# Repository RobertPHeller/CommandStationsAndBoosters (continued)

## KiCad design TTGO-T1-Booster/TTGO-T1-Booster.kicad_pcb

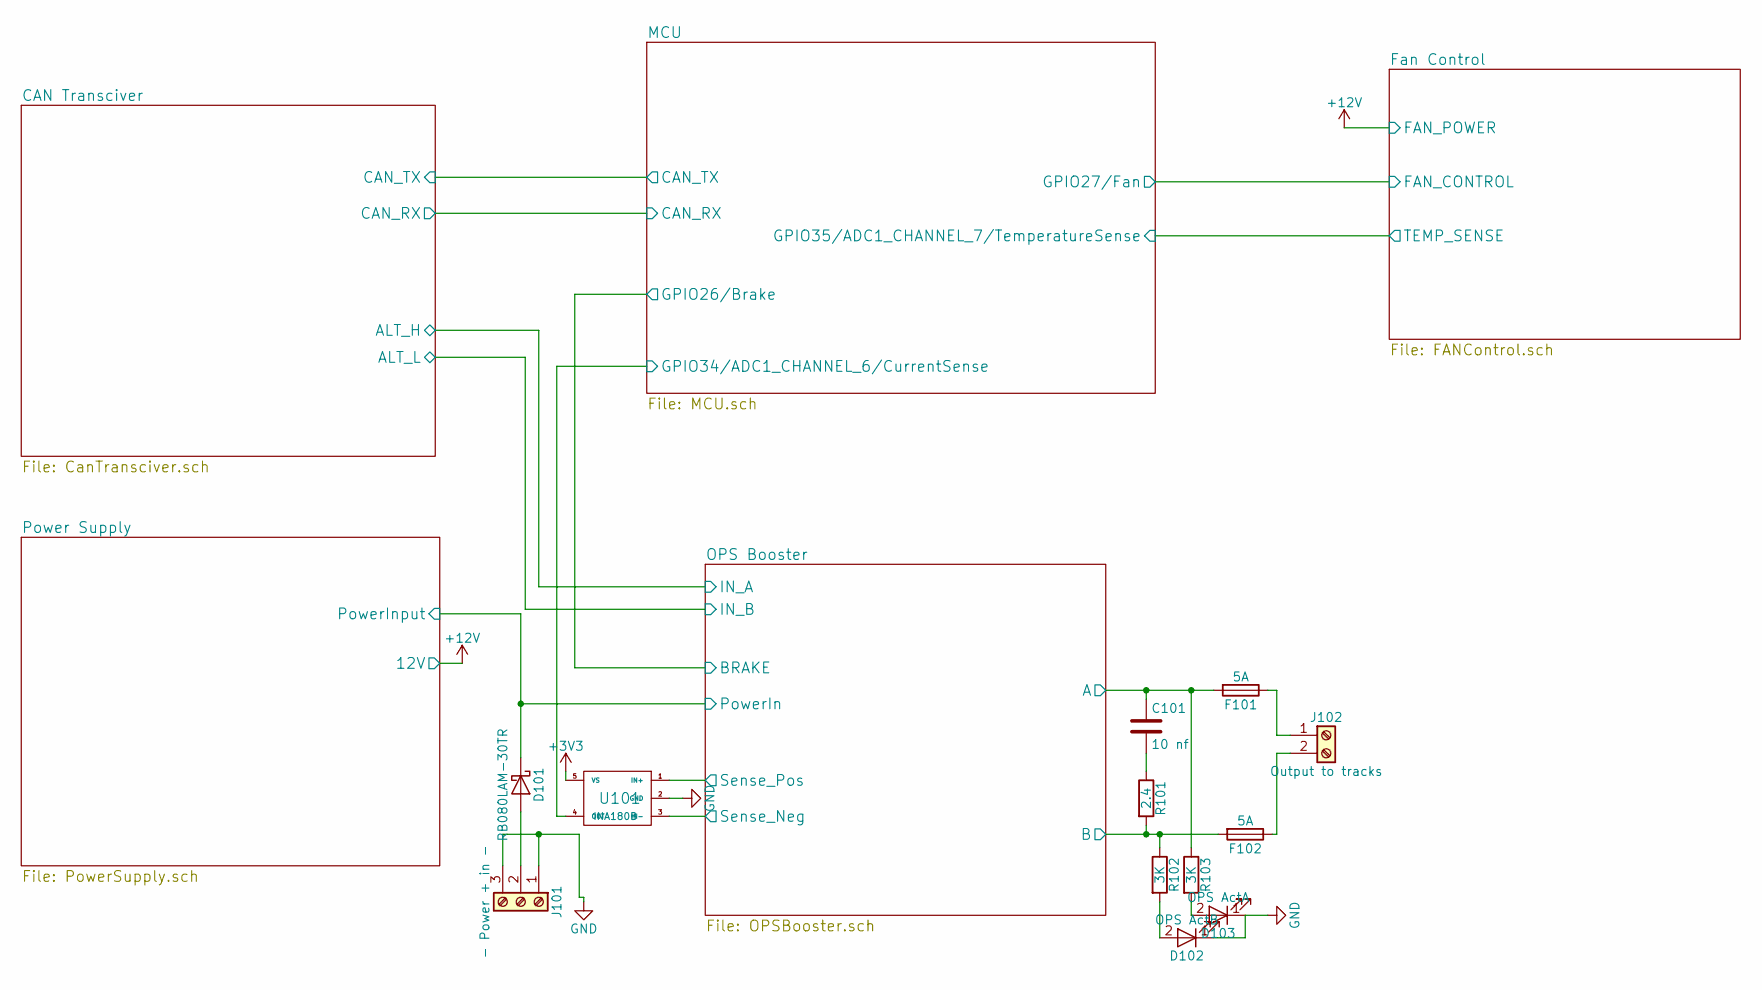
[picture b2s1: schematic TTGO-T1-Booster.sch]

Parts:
C101: 10 nf; C_1206; Mouser Part Number 791-1206B103K500CT
D101: RB080LAM-30TR; PMDTM; Mouser Part Number 755-RB080LAM-30TR
D102: OPS ActB; LED_0603; Mouser Part Number 710-150060RS75000
D103: OPS ActA; LED_0603; Mouser Part Number 710-150060GS75000
F101, F102: 5A; MFR500; Mouser Part Number 652-MFR500
J101: - Power + in -; TerminalBlock_Pheonix_PT-3.5mm_3pol; Mouser Part Number 651-544225
J102: Output to tracks; TerminalBlock_Pheonix_PT-3.5mm_2pol; Mouser Part Number 651-5442248
R101: 2.4; R_1206; Mouser Part Number 71-CRCW12062R40FKEA
R102: 3K; R_0603
R103: 3K; R_0603; Mouser Part Number 660-RN73H1JT3001F100
U101: INA180B; SOT-23-5

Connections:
/MCU/GPIO34/ADC1_CHANNEL_6/CurrentSense: U101.4 (OUT); also elsewhere on the board
/OPS Booster/A: C101.1, F101.2, R103.1; also elsewhere on the board
/OPS Booster/B: F102.2, R101.2, R102.1; also elsewhere on the board
/OPS Booster/PowerIn: D101.1 (K), U101.1 (IN+); also elsewhere on the board
/OPS Booster/Sense_Neg: U101.3 (IN-); also elsewhere on the board
GND: D102.1 (K), D103.1 (K), J101.1, J101.3, U101.2 (GND); also elsewhere on the board
unnamed: C101.2, R101.1
unnamed: D101.2 (A), J101.2
unnamed: D102.2 (A), R102.2
unnamed: D103.2 (A), R103.2
unnamed: F101.1, J102.1
unnamed: F102.1, J102.2

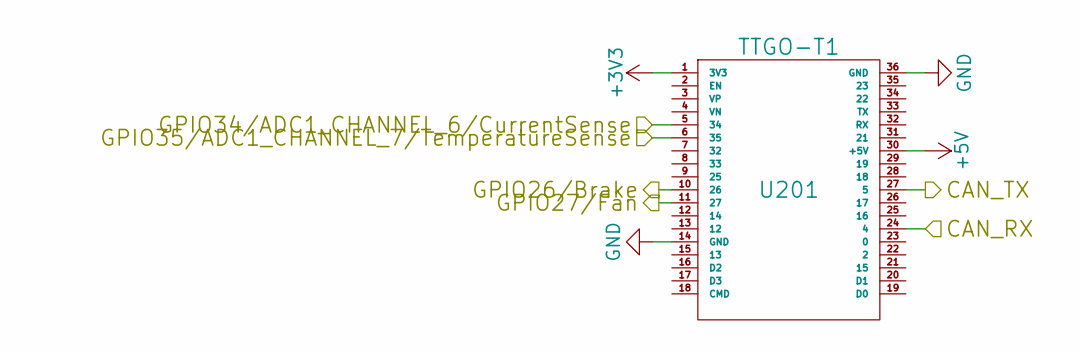
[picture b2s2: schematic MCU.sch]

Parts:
U201: TTGO-T1; TIGO-T1

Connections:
+5V: U201.30 (+5V); also elsewhere on the board
/CAN Transciver/CAN_RX: U201.24 (4); also elsewhere on the board
/CAN Transciver/CAN_TX: U201.27 (5); also elsewhere on the board
/Fan Control/FAN_CONTROL: U201.11 (27); also elsewhere on the board
/MCU/GPIO34/ADC1_CHANNEL_6/CurrentSense: U201.5 (34); also elsewhere on the board
/MCU/GPIO35/ADC1_CHANNEL_7/TemperatureSense: U201.6 (35); also elsewhere on the board
/OPS Booster/BRAKE: U201.10 (26); also elsewhere on the board
GND: U201.14 (GND), U201.36 (GND); also elsewhere on the board

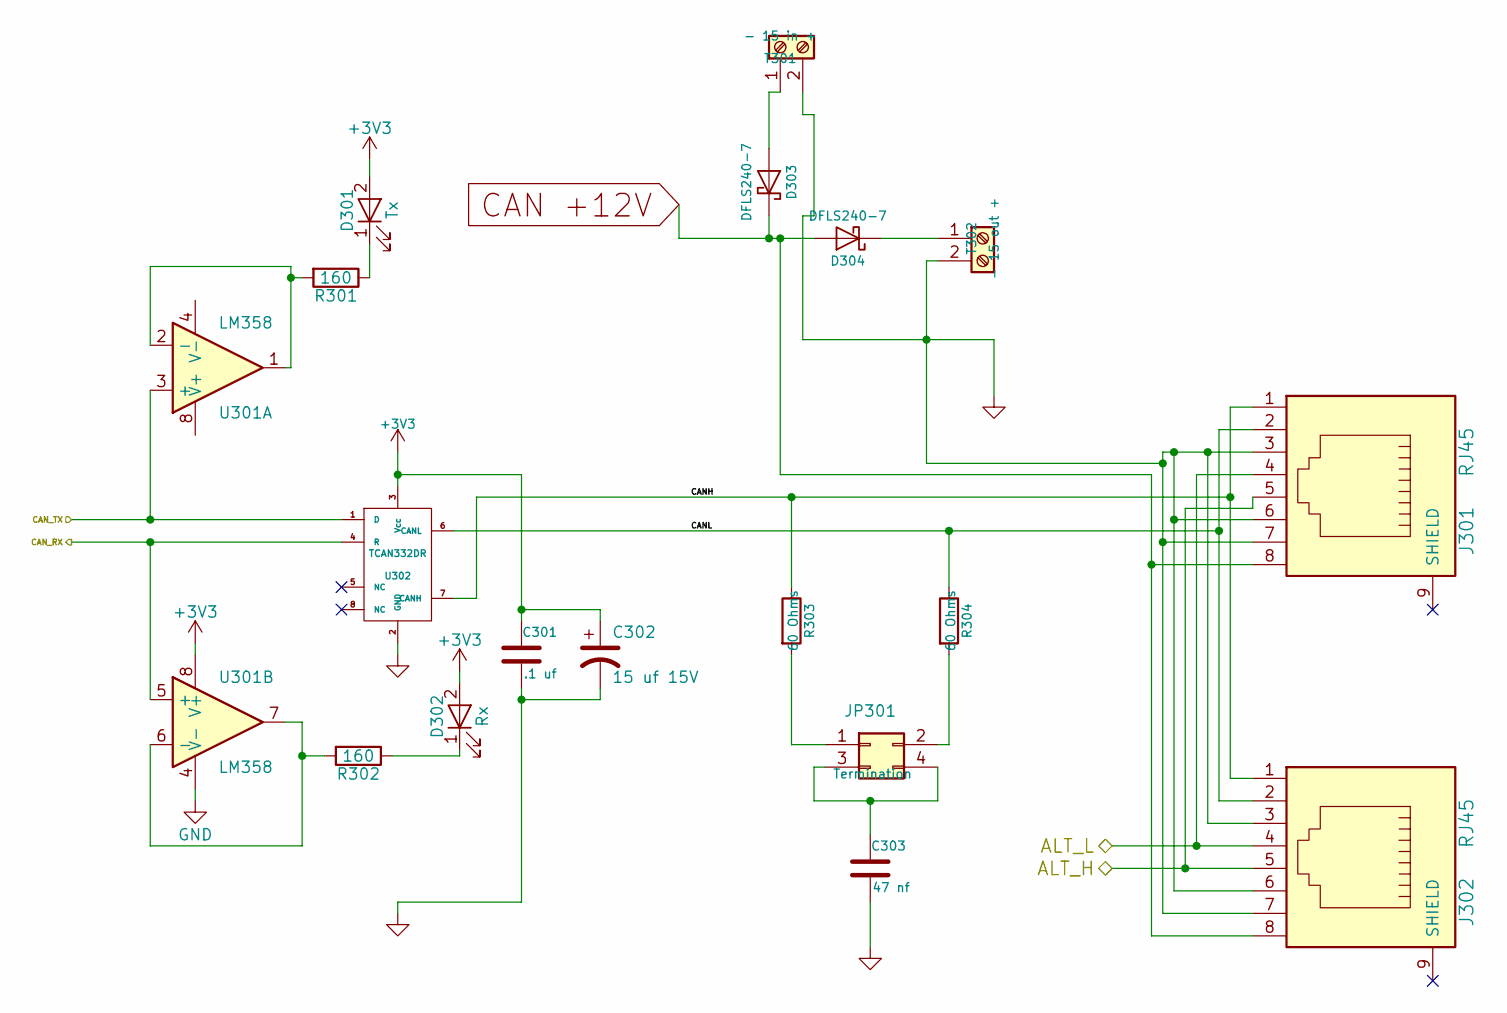
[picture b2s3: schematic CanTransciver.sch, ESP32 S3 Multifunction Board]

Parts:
C301: .1 uf; C_0603; Mouser Part Number 710-885012206095
C302: 15 uf 15V; CP_Elec_4x5.7; Mouser Part Number 647-UUD1C150MCL
C303: 47 nf; C_0603; Mouser Part Number 710-885012206093
D301: Tx; LED_0603; Mouser Part Number 710-150060SS75000
D302: Rx; LED_0603; Mouser Part Number 710-150060YS75000
D303, D304: DFLS240-7; D_PowerDI-123; Mouser Part Number 621-DFLS240-7
J301, J302: RJ45; RJ45_8N-S; Mouser Part Number 710-615008144221
JP301: Termination; Pin_Header_Straight_2x02_Pitch2.54mm; Mouser Part Number 649-67997-404HLF
R301, R302: 160; R_0603; Mouser Part Number 603-AC0603JR-07160RL
R303, R304: 60 Ohms; R_1206; Mouser Part Number 71-CRCW120660R0KNAIF
T301: - 15 in +; TerminalBlock_Pheonix_MPT-2.54mm_2pol; Mouser Part Number 651-1725656
T302: - 15 out +; TerminalBlock_Pheonix_MPT-2.54mm_2pol; Mouser Part Number 651-1725656
U301: LM358; SOIC-8_3.9x4.9mm_Pitch1.27mm; Mouser Part Number 595-LM358BIDR
U302: TCAN332DR; SOIC-8_3.9x4.9mm_Pitch1.27mm; Mouser Part Number 595-TCAN332DR

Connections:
/CAN Transciver/ALT_H: J301.5, J302.5; also elsewhere on the board
/CAN Transciver/ALT_L: J301.4, J302.4; also elsewhere on the board
/CAN Transciver/CANH: J301.1, J302.1, R303.1, U302.7 (CANH)
/CAN Transciver/CANL: J301.2, J302.2, R304.1, U302.6 (CANL)
/CAN Transciver/CAN_RX: U301.5 (+), U302.4 (R); also elsewhere on the board
/CAN Transciver/CAN_TX: U301.3 (+), U302.1 (D); also elsewhere on the board
CAN +12V: D303.1 (K), D304.2 (A), J301.8, J302.8
GND: C301.2, C302.2, C303.2, J301.3, J301.6, J301.7, J302.3, J302.6, J302.7, T301.2, T302.2, U301.4 (V-), U302.2 (GND); also elsewhere on the board
unnamed: C303.1, JP301.3, JP301.4
unnamed: D301.1 (K), R301.1
unnamed: D302.1 (K), R302.1
unnamed: D303.2 (A), T301.1
unnamed: D304.1 (K), T302.1
unnamed: JP301.1, R303.2
unnamed: JP301.2, R304.2
unnamed: R301.2, U301.1, U301.2 (-)
unnamed: R302.2, U301.6 (-), U301.7

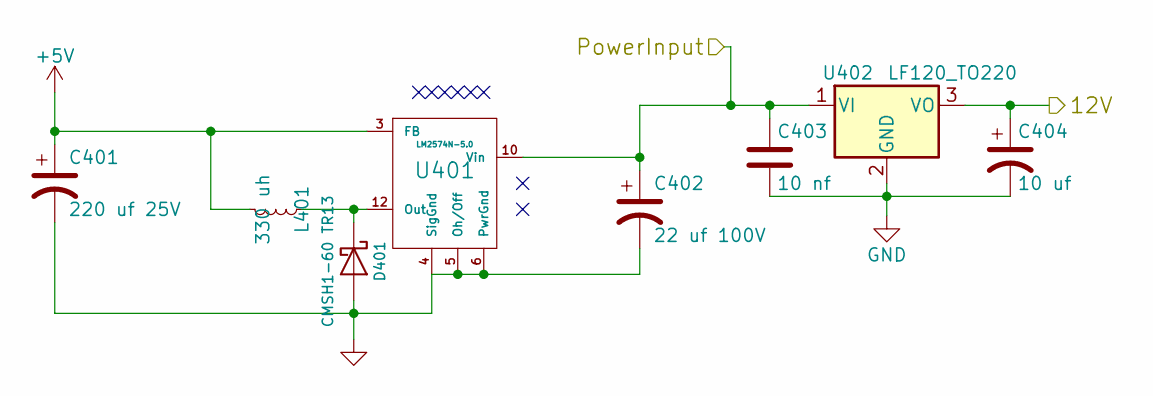
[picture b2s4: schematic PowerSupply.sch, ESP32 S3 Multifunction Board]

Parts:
C401: 220 uf 25V; CP_Elec_8x10; Mouser Part Number 647-UWT1E221MNL1GS
C402: 22 uf 100V; CP_Elec_8x10; Mouser Part Number 647-UUX2A220MNL6GS
C403: 10 nf; C_1206; Mouser Part Number 791-1206B103K500CT
C404: 10 uf; CP_Elec_5x5.3; Mouser Part Number 710-865230542002
D401: CMSH1-60 TR13; D_SMB; Mouser Part Number 610-CMSH1-60TR13
L401: 330 uh; SRN1060; Mouser Part Number 652-SRN1060-331M
U401: LM2574N-5.0; SOIC-14_7.4x8.7mm_Pitch1.27mm; Mouser Part Number 926-LM2574MX-5.0NOPB
U402: LF120_TO220; TO-252-2; Mouser Part Number 511-LF120ABDT-TR

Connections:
+5V: C401.1, L401.2, U401.3 (FB); also elsewhere on the board
+12V: C404.1, U402.3 (VO); also elsewhere on the board
/OPS Booster/PowerIn: C402.1, C403.1, U401.10 (Vin), U402.1 (VI); also elsewhere on the board
GND: C401.2, C402.2, C403.2, C404.2, D401.2 (A), U401.4 (SigGnd), U401.5 (Oh/Off), U401.6 (PwrGnd), U402.2 (GND); also elsewhere on the board
unnamed: D401.1 (K), L401.1, U401.12 (Out)

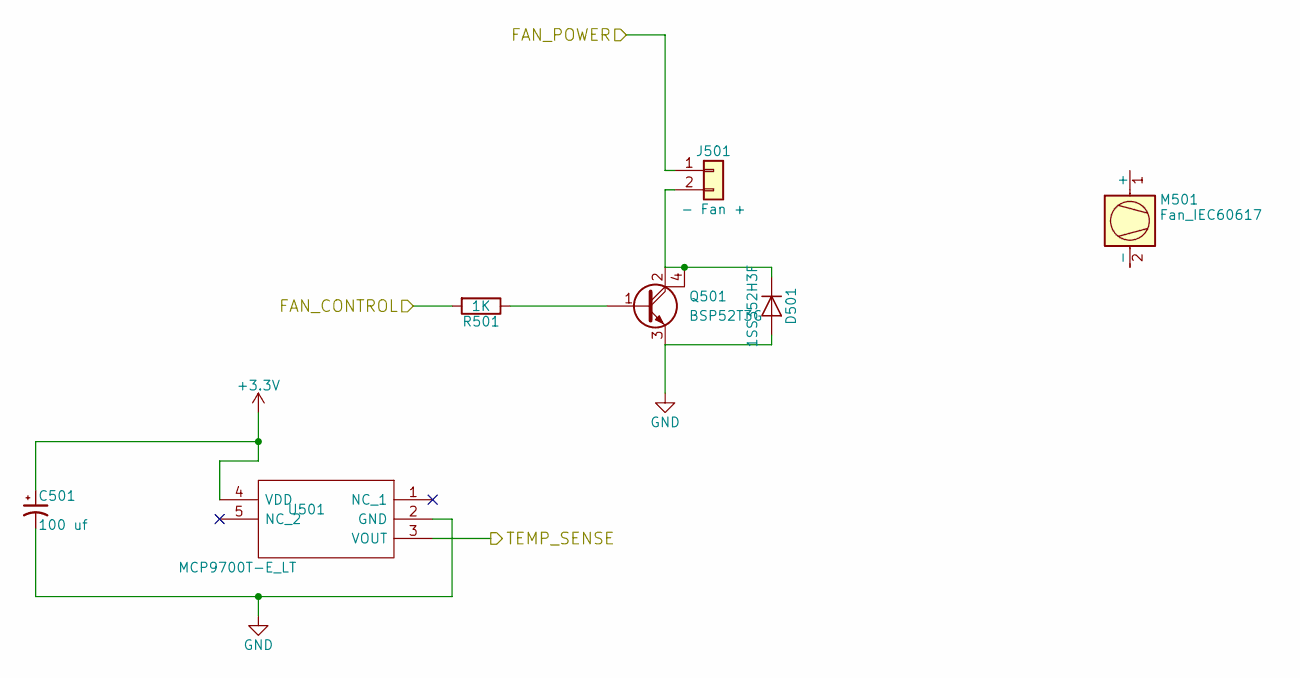
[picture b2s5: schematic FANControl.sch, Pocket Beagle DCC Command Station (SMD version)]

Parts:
C501: 100 uf; C_0603; Mouser Part Number 603-CC603KPX7R9BB104
D501: 1SS352H3F; D_SOD-323; Mouser Part Number 757-1SS352H3F
J501: - Fan +; Pin_Header_Straight_1x02_Pitch2.54mm; Mouser Part Number 538-42375-1855
M501: Fan_IEC60617; 25mmFanMount; Mouser Part Number 490-CFM2510B1100-218
Q501: BSP52T3G; SOT-223; Mouser Part Number 863-BSP52T3G
R501: 1K; R_0603; Mouser Part Number 279-CRGCQ0603F1K0
U501: MCP9700T-E_LT; SOT65P210X110-5N; Mouser Part Number 579-MCP9700T-E/LT

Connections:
+12V: J501.1; also elsewhere on the board
/Fan Control/FAN_CONTROL: R501.2; also elsewhere on the board
/MCU/GPIO35/ADC1_CHANNEL_7/TemperatureSense: U501.3 (VOUT); also elsewhere on the board
GND: C501.2, D501.2 (A), Q501.3 (E), U501.2 (GND); also elsewhere on the board
unnamed: D501.1 (K), J501.2, Q501.2 (C), Q501.4 (C2)
unnamed: Q501.1 (B), R501.1

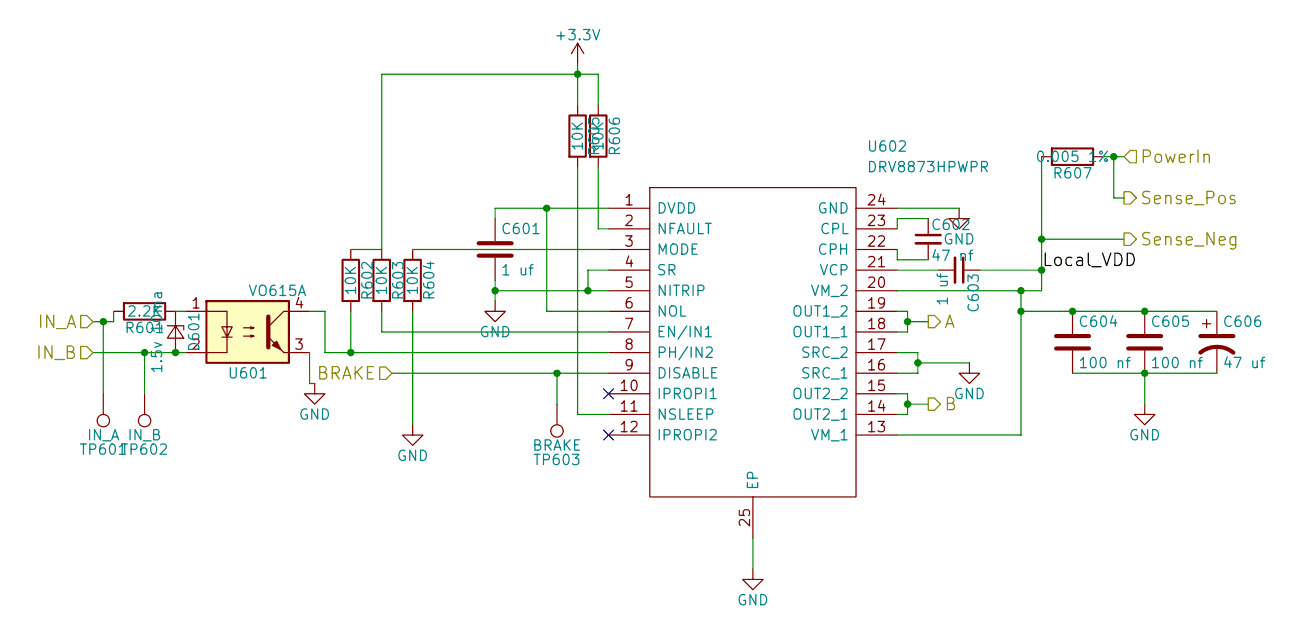
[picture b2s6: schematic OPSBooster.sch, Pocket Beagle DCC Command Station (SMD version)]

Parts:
C601, C603: 1 uf; C_0603; Mouser Part Number 963-GMK107AB7105KAHT
C602: 47 nf; C_0603; Mouser Part Number 963-GMK107BJ473KAHT
C604, C605: 100 nf; C_0603; Mouser Part Number 603-CC603KPX7R9BB104
C606: 47 uf; CP_Elec_6.3x5.3; Mouser Part Number 710-865080543009
D601: 1.5v 10ma; D_SOD-323; Mouser Part Number 610-CMDZ1L8TR
R601: 2.2K; R_0603; Mouser Part Number 603-AC0603FR-072K2L
R602, R603, R604, R605, R606: 10K; R_0603; Mouser Part Number 279-CRGCQ0603F10K
R607: 0.005 1%; R_0612; Mouser Part Number 71-WSKW0612L5000FEA
TP601: IN_A; Measurement_Point_Round-SMD-Pad_Big
TP602: IN_B; Measurement_Point_Round-SMD-Pad_Big
TP603: BRAKE; Measurement_Point_Round-SMD-Pad_Big
U601: VO615A; SO-4_7.6x3.6mm_Pitch2.54mm; Mouser Part Number 78-VO615A-7X017T
U602: DRV8873HPWPR; SOP65P640X120-25N; Mouser Part Number 595-DRV8873HPWPR

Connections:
/CAN Transciver/ALT_H: R601.2, TP601.1; also elsewhere on the board
/CAN Transciver/ALT_L: D601.2 (A), TP602.1, U601.2; also elsewhere on the board
/OPS Booster/A: U602.18 (OUT1_1), U602.19 (OUT1_2); also elsewhere on the board
/OPS Booster/B: U602.14 (OUT2_1), U602.15 (OUT2_2); also elsewhere on the board
/OPS Booster/BRAKE: TP603.1, U602.9 (DISABLE); also elsewhere on the board
/OPS Booster/PowerIn: R607.1; also elsewhere on the board
/OPS Booster/Sense_Neg: C603.1, C604.1, C605.1, C606.1, R607.2, U602.13 (VM_1), U602.20 (VM_2); also elsewhere on the board
GND: C601.2, C604.2, C605.2, C606.2, R604.2, U601.3, U602.4 (SR), U602.5 (NITRIP), U602.16 (SRC_1), U602.17 (SRC_2), U602.24 (GND), U602.25 (EP); also elsewhere on the board
unnamed: C601.1, U602.1 (DVDD), U602.6 (NOL)
unnamed: C602.1, U602.23 (CPL)
unnamed: C602.2, U602.22 (CPH)
unnamed: C603.2, U602.21 (VCP)
unnamed: D601.1 (K), R601.1, U601.1
unnamed: R602.2, U601.4, U602.8 (PH/IN2)
unnamed: R603.2, U602.7 (EN/IN1)
unnamed: R604.1, U602.3 (MODE)
unnamed: R605.2, U602.11 (NSLEEP)
unnamed: R606.2, U602.2 (NFAULT)

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
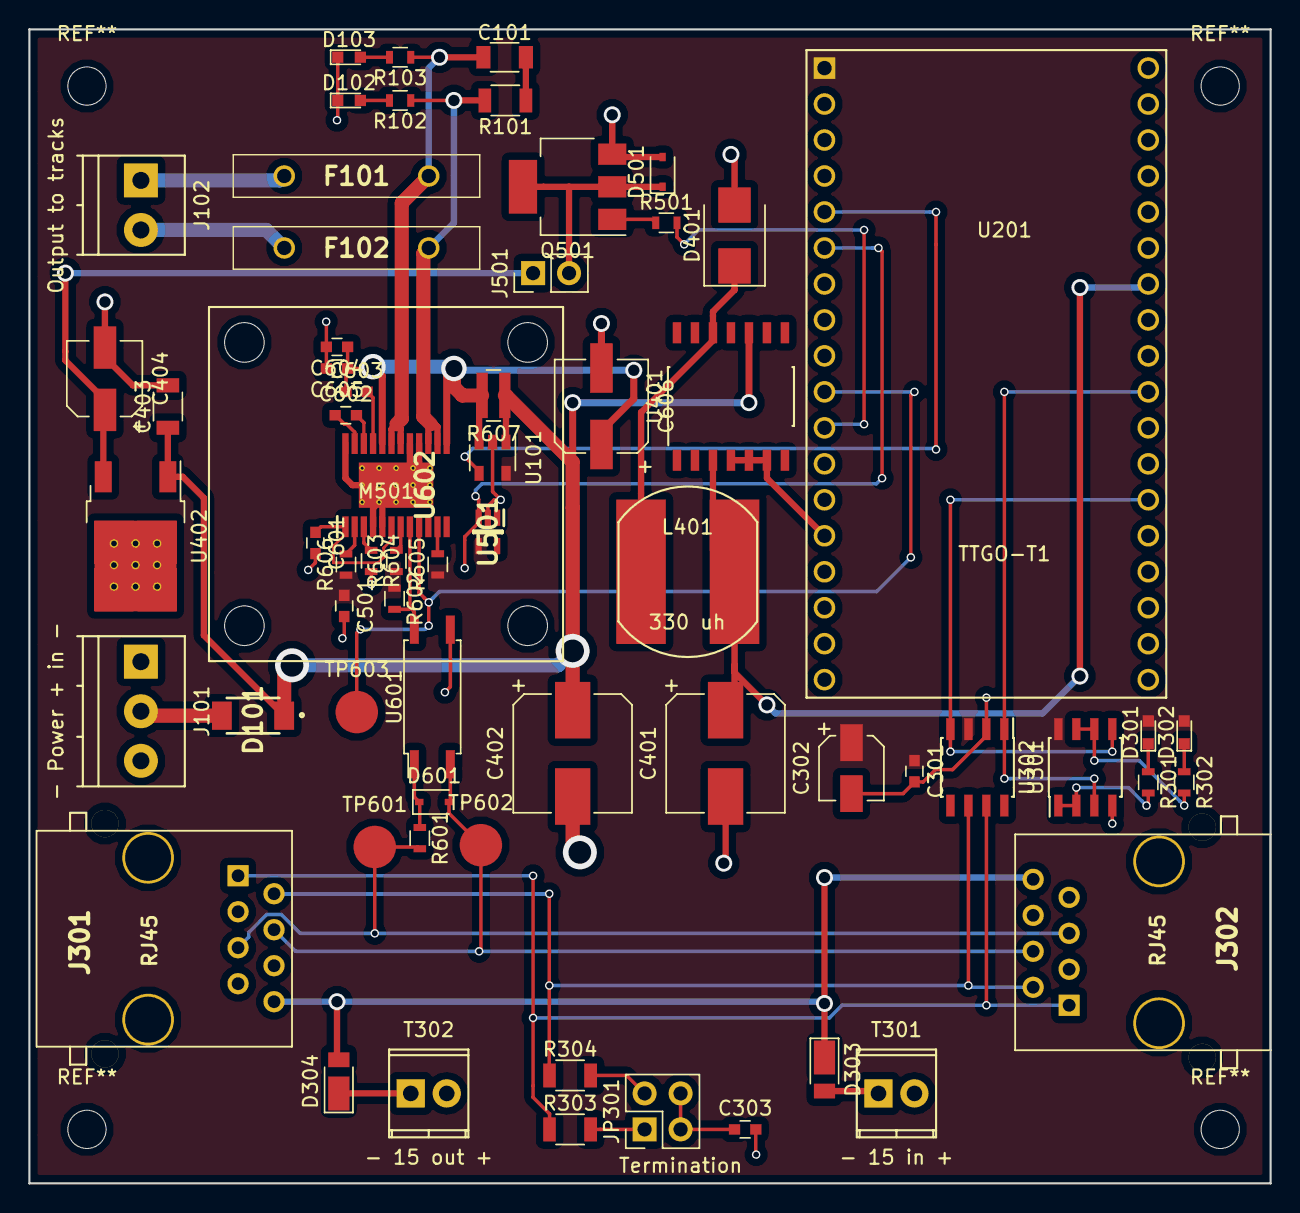
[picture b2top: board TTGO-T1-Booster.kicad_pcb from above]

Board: 2 copper layers, 87.6 x 81.5 mm, 65 parts (0 on the bottom side), 47 nets.

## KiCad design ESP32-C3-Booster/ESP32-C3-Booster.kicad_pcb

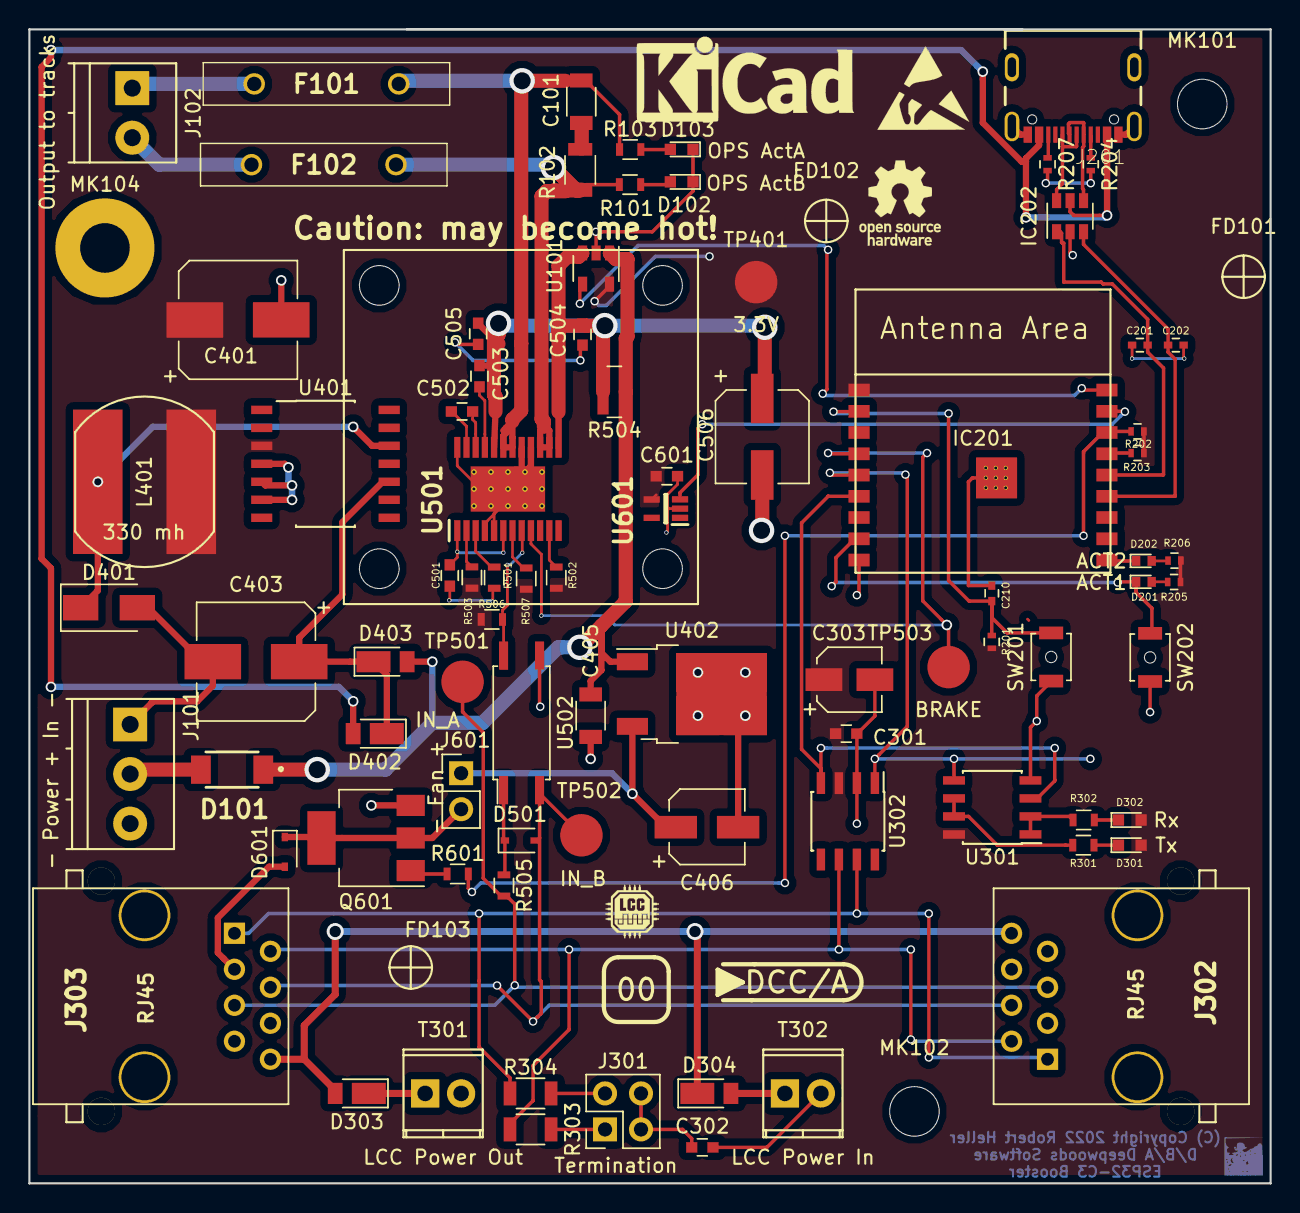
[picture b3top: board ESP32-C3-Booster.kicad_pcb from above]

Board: 2 copper layers, 87.6 x 81.5 mm, 90 parts (0 on the bottom side), 60 nets.

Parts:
C101, C405: 10 nf; C_1206
C201, C202: 22pf; C_0402
C210: 1uf; C_0402
C301, C504, C505: 100 nf; C_0603
C302, C502: 47 nf; C_0603
C303: 15 uf 15V; CP_Elec_4x5.8
C401: 220 uf 25V; CP_Elec_8x10
C403: 22 uf 100V; CP_Elec_8x10
C406: 10 uf; CP_Elec_5x5.3
C501, C503: 1 uf; C_0603
C506: 47 uf; CP_Elec_6.3x5.3
C601: 100 uf; C_0603
D101: RB080LAM-30TR; PMDTM
D102: OPS ActB; LED_0603
D103: OPS ActA; LED_0603
D201: ACT1; LED_0402
D202: ACT2; LED_0402
D301: Tx; LED_0603
D302: Rx; LED_0603
D303, D304, D402, D403: DFLS240; D_PowerDI-123
D401: CMSH1-60; D_SMA
D501: 1.5v 10ma; D_SOD-323
D601: 1SS352H3F; D_SOD-323
F101, F102: 5A; MFR500
FD101, FD102, FD103: Fiducial; Fiducial_classic_Small_SilkscreenTop_Type1
IC201: ESP32-C3-WROOM
IC202: USBLC6-2SC6; SOT-23-6
J101: - Power + In -; TerminalBlock_Pheonix_PT-3.5mm_3pol
J102: Output to tracks; TerminalBlock_Pheonix_PT-3.5mm_2pol
J201: USB_C; GCT_USB4105-GF-A
J301: Termination; Pin_Header_Straight_2x02_Pitch2.54mm
J302, J303: RJ45; RJ45_8N-S
J601: - Fan +; Pin_Header_Straight_1x02_Pitch2.54mm
L401: 330 mh; SRN1060
M601: Fan_IEC60617; 25mmFanMount
MK101, MK102: Mounting_Hole; MountingHole_3.5mm
MK104: Mounting_Hole_PAD; MountingHole_3.5mm_Pad
Q601: BSP52T3G; SOT-223
R101, R103: 3K; R_0603
R102: 2.4; R_1206
R201, R202, R203: 10K; R_0402
R204, R207: 5.1K; R_0402
R205, R206: 270; R_0402
R301, R302: 160; R_0603
R303, R304: 60; R_1206
R501, R502, R503, R506, R507: 10K; R_0603
R504: 0.005 1%; R_0612
R505: 2.2K; R_0603
R601: 1K; R_0603
SW201: RESET; SW_SPST_B3U-1000P-B
SW202: BOOT; SW_SPST_B3U-1000P-B
T301: LCC Power Out; TerminalBlock_Pheonix_MPT-2.54mm_2pol
T302: LCC Power In; TerminalBlock_Pheonix_MPT-2.54mm_2pol
TP401: 3.3V; Measurement_Point_Round-SMD-Pad_Big
TP501: IN_A; Measurement_Point_Round-SMD-Pad_Big
TP502: IN_B; Measurement_Point_Round-SMD-Pad_Big
TP503: BRAKE; Measurement_Point_Round-SMD-Pad_Big
U101: INA180B; SOT-23-5
U301: LM358; SOIC-8_3.9x4.9mm_Pitch1.27mm
U302: TCAN332DR; SOIC-8_3.9x4.9mm_Pitch1.27mm
U401: LM2574HVM-3.3; SOIC-14_7.4x8.7mm_Pitch1.27mm
U402: LF120_TO220; TO-252-2
U501: DRV8873HPWPR; SOP65P640X120-25N
U502: VO615A; SO-4_7.6x3.6mm_Pitch2.54mm
U601: MCP9700T-E_LT; SOT65P210X110-5N

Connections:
+3V3: C301.1, C303.1, C401.1, C601.1, D301.2, D302.2, IC201.1, L401.2, R201.1, R202.1, R203.1, R205.1, R206.1, R502.1, R503.1, R506.1, R507.1, TP401.1, U101.5, U301.8, U302.3, U401.3, U601.4
+12V: C406.1, J601.1, U402.3
/CAN Transeiver/ALT_H: J302.5, J303.5, R505.2, TP501.1
/CAN Transeiver/ALT_L: D501.2, J302.4, J303.4, TP502.1, U502.2
/CAN Transeiver/CAN_RX: IC201.6, U301.3, U302.4
/CAN Transeiver/CAN_TX: IC201.5, U301.5, U302.1
/ESP32-C3 MCU/ACT1/GPIO9: D201.1, IC201.8, SW202.1
/ESP32-C3 MCU/ACT2/GPIO10: D202.1, IC201.10
/ESP32-C3 MCU/D+: C201.2, IC201.14, IC202.1
/ESP32-C3 MCU/D-: C202.1, IC201.13, IC202.3
/ESP32-C3 MCU/GPIO0/A1/CurrentSense: IC201.18, U101.4
/ESP32-C3 MCU/GPIO1/A2/TermpSense: IC201.17, U601.3
/ESP32-C3 MCU/RESET: C210.1, IC201.2, R201.2, SW201.2
/Fan Controls/FAN_CONTROL: IC201.16, R202.2, R601.2
/OPS Driver/A: C101.1, F101.1, R103.1, U501.18, U501.19
/OPS Driver/B: F102.1, R101.1, R102.2, U501.14, U501.15
/OPS Driver/BRAKE: IC201.4, TP503.1, U501.9
/OPS Driver/Sense_Neg: C503.1, C504.1, C505.1, C506.1, R504.2, U101.3, U501.13, U501.20
/Power Supply/Power Input: C405.1, D101.1, D403.2, R504.1, U101.1, U402.1
GND: C201.1, C202.2, C210.2, C301.2, C302.2, C303.2, C401.2, C403.2, C405.2, C406.2, C501.2, C504.2, C505.2, C506.2, C601.2, D102.1, D103.1, D401.2, D601.2, IC201.9, IC201.19, IC202.2, J101.1, J101.3, J201.A1/B, J201.B1/A, J201.G1, J201.G2, J201.G3, J201.G4, J302.3, J302.6, J302.7, J303.3, J303.6, J303.7, Q601.3, R204.2, R207.2, R501.2, SW201.1, SW202.2, T301.2, T302.2, U101.2, U301.4, U302.2, U401.4, U401.5, U401.6, U402.2, U501.4, U501.5, U501.16, U501.17, U501.24, U501.25, U502.3, U601.2
unnamed: C101.2, R102.1
unnamed: C302.1, J301.3, J301.4
unnamed: C403.1, D402.1, D403.1, U401.10
unnamed: C501.1, U501.1, U501.6
unnamed: C502.1, U501.23
unnamed: C502.2, U501.22
unnamed: C503.2, U501.21
unnamed: D101.2, J101.2
unnamed: D102.2, R101.2
unnamed: D103.2, R103.2
unnamed: D201.2, R205.2
unnamed: D202.2, R206.2
unnamed: D301.1, R301.1
unnamed: D302.1, R302.1
unnamed: D303.1, T301.1
unnamed: D303.2, D304.1, J302.8, J303.8
unnamed: D304.2, T302.1
unnamed: D401.1, L401.1, U401.12
unnamed: D501.1, R505.1, U502.1
unnamed: D601.1, J601.2, Q601.2, Q601.4
unnamed: F101.2, J102.1
unnamed: F102.2, J102.2
unnamed: IC201.15, R203.2
unnamed: IC202.4, J201.A7, J201.B7
unnamed: IC202.6, J201.A6, J201.B6
unnamed: J201.A5, R204.1
unnamed: J201.B5, R207.1
unnamed: J301.1, R303.2
unnamed: J301.2, R304.2
unnamed: J302.1, J303.1, R304.1, U302.7
unnamed: J302.2, J303.2, R303.1, U302.6
unnamed: Q601.1, R601.1
unnamed: R301.2, U301.6, U301.7
unnamed: R302.2, U301.1, U301.2
unnamed: R501.1, U501.3
unnamed: R502.2, U501.11
unnamed: R503.2, U501.2
unnamed: R506.2, U501.8, U502.4
unnamed: R507.2, U501.7
VBUS: D402.2, IC202.5, J201.A4/B, J201.B4/A

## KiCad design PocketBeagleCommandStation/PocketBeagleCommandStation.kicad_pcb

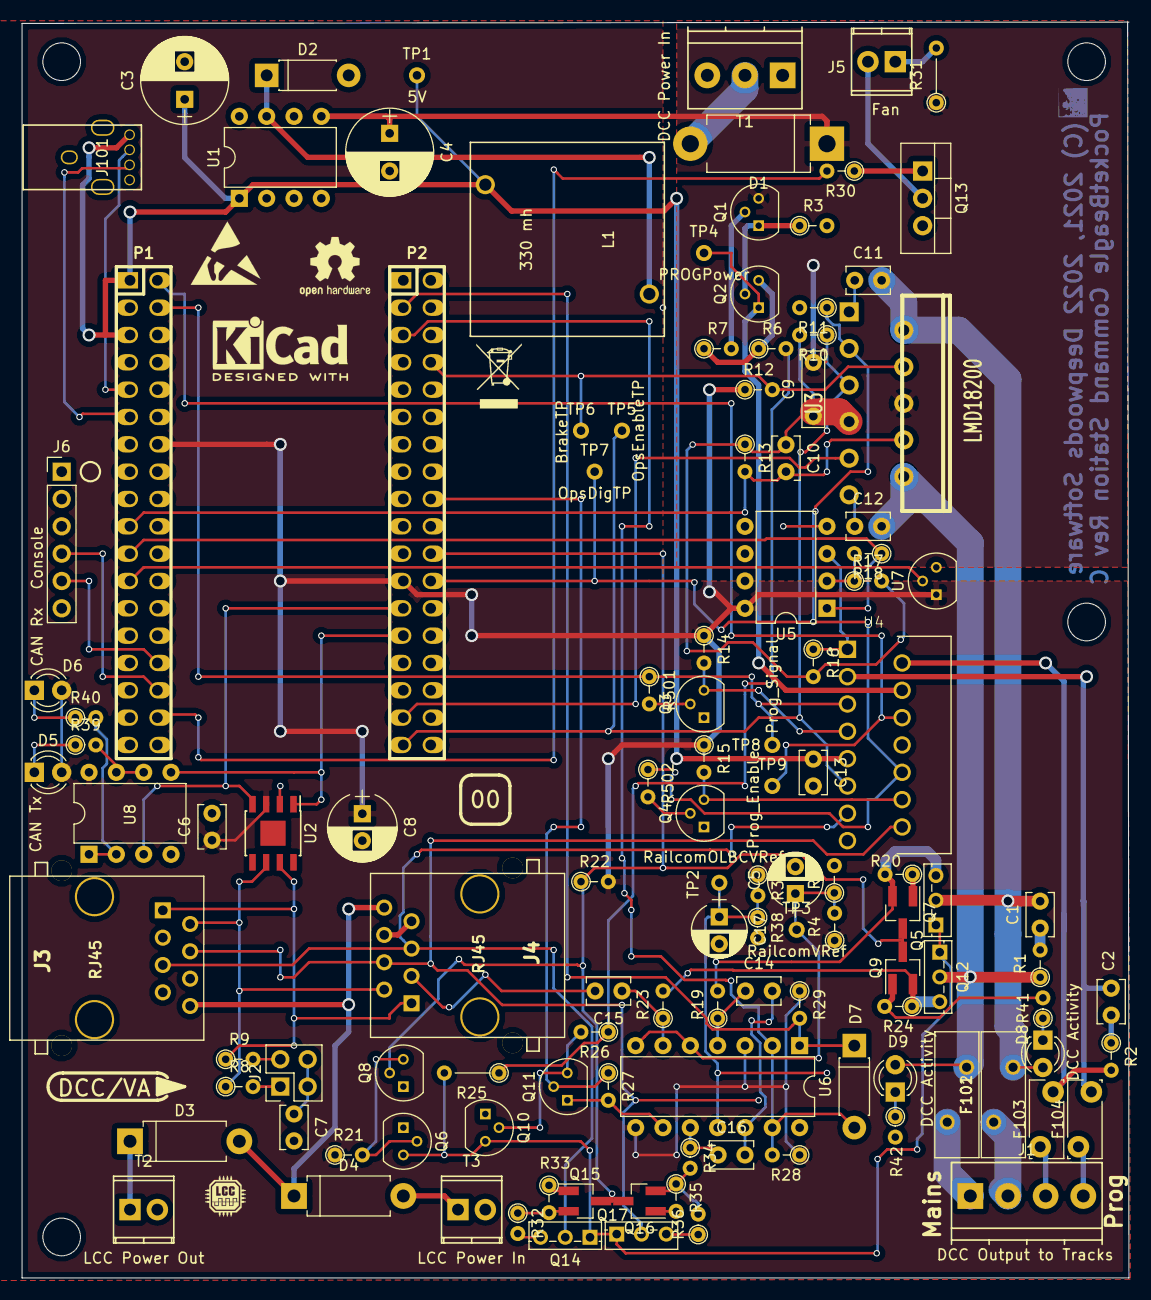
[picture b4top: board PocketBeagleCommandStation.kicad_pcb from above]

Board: 2 copper layers, 102.9 x 116.7 mm, 121 parts (0 on the bottom side), 81 nets.

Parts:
C1, C2, C11, C12: 10 nf; C_Rect_L4.0mm_W2.5mm_P2.50mm
C3: 220 uf 25V; CP_Radial_D8.0mm_P3.50mm
C4: 22 uf 100V; CP_Radial_D8.0mm_P3.50mm
C5, C17: 1 uf; CP_Radial_D5.0mm_P2.50mm
C6: .1 uf; C_Rect_L4.0mm_W2.5mm_P2.50mm
C7: 47 nf; C_Rect_L4.0mm_W2.5mm_P2.50mm
C8: 15 uf 15V; CP_Radial_D6.3mm_P2.50mm
C9: 1 uf; C_Rect_L7.0mm_W2.0mm_P5.00mm
C10, C13: 100 nf; C_Rect_L4.0mm_W2.5mm_P2.50mm
C14, C15, C16: 33pf; C_Rect_L4.0mm_W2.5mm_P2.50mm
D1: SB530; D_DO-201AD_P12.70mm_Horizontal
D2: SB160; D_DO-41_SOD81_P7.62mm_Horizontal
D3, D4: SB240; D_DO-15_P10.16mm_Horizontal
D5: CAN Tx; LED_D3.0mm
D6: CAN Rx; LED_D3.0mm
D7: 1N5817; D_DO-41_SOD81_P7.62mm_Horizontal
D8, D9: DCC Activity; LED_D3.0mm
F101, F102: 3A; Fuse_BelFuse_0ZRE0033FF_L11.4mm_W3.8mm
F103, F104: 300ma; Fuse_Bourns_MF-RG300
J1: DCC Output to Tracks; TerminalBlock_Pheonix_PT-3.5mm_4pol
J2: Termination; Pin_Header_Straight_2x02_Pitch2.54mm
J3, J4: RJ45; RJ45_8N-S
J5: Fan; TerminalBlock_Pheonix_MPT-2.54mm_2pol
J6: Console; Pin_Header_Straight_1x06_Pitch2.54mm
J101: USB_A; USB-A-UPRIGHT
L1: 330 mh; PE-LowProfile
P1, P2: POCKETBEAGLE-Header; pin_socket_18x2
Q1: 2N3906; TO-92_Molded_Narrow
Q2: TP0606; TO-92_Molded_Narrow
Q3, Q4: 2N3904; TO-92_Molded_Narrow
Q5, Q12, Q14, Q17: STD12NF06; TO-251_IPAK_Vertical
Q6, Q8, Q10, Q11: 2N7000; TO-92_Molded_Narrow
Q7, Q9, Q15, Q16: DTC143E; SOT-23_Handsoldering
Q13: TIP120; TO-220_Vertical
R1, R2, R20, R24: 2.4 Ohms; R_Axial_DIN0204_L3.6mm_D1.6mm_P2.54mm_Vertical
R3, R7: 4.7K Ohms; R_Axial_DIN0204_L3.6mm_D1.6mm_P2.54mm_Vertical
R4: 3.24K Ohms, 1%; R_Axial_DIN0204_L3.6mm_D1.6mm_P2.54mm_Vertical
R5: 19.1 Ohms 1%; R_Axial_DIN0204_L3.6mm_D1.6mm_P2.54mm_Vertical
R6: 2.7 Ohms; R_Axial_DIN0204_L3.6mm_D1.6mm_P2.54mm_Vertical
R8, R9: 60 Ohms; R_Axial_DIN0204_L3.6mm_D1.6mm_P2.54mm_Vertical
R10, R11, R12, R21, R22: 20K Ohms; R_Axial_DIN0204_L3.6mm_D1.6mm_P2.54mm_Vertical
R13: 1.5K Ohms; R_Axial_DIN0204_L3.6mm_D1.6mm_P2.54mm_Vertical
R14, R15, R17, R30: 1K Ohms; R_Axial_DIN0204_L3.6mm_D1.6mm_P2.54mm_Vertical
R16: .15 Ohms; R_Axial_DIN0204_L3.6mm_D1.6mm_P2.54mm_Vertical
R18, R19, R23, R26: 10K Ohms; R_Axial_DIN0204_L3.6mm_D1.6mm_P2.54mm_Vertical
R25: 1.5K Ohms 1/2W; R_Axial_DIN0204_L3.6mm_D1.6mm_P5.08mm_Vertical
R27, R28, R29: 2.4K Ohms; R_Axial_DIN0204_L3.6mm_D1.6mm_P2.54mm_Vertical
R31: 56 Ohms 1/2 watt; R_Axial_DIN0204_L3.6mm_D1.6mm_P5.08mm_Vertical
R32: 24.9; R_Axial_DIN0204_L3.6mm_D1.6mm_P1.90mm_Vertical
R33, R35: 24.9 Ohms; R_Axial_DIN0204_L3.6mm_D1.6mm_P2.54mm_Vertical
R34: 10K Ohms; R_Axial_DIN0204_L3.6mm_D1.6mm_P1.90mm_Vertical
R36: 24.9 Ohms; R_Axial_DIN0204_L3.6mm_D1.6mm_P1.90mm_Vertical
R37: 3.24K Ohms, 1%; R_Axial_DIN0204_L3.6mm_D1.6mm_P1.90mm_Vertical
R38: 102 Ohms 1%; R_Axial_DIN0204_L3.6mm_D1.6mm_P1.90mm_Vertical
R39, R40: 160 Ohms; R_Axial_DIN0204_L3.6mm_D1.6mm_P1.90mm_Vertical
R41, R42: 3K Ohms; R_Axial_DIN0204_L3.6mm_D1.6mm_P1.90mm_Vertical
R501, R502: 1K; R_Axial_DIN0204_L3.6mm_D1.6mm_P2.54mm_Vertical
T1: DCC Power In; TerminalBlock_Pheonix_PT-3.5mm_3pol
T2: LCC Power Out; TerminalBlock_Pheonix_MPT-2.54mm_2pol
T3: LCC Power In; TerminalBlock_Pheonix_MPT-2.54mm_2pol
TP1: 5V; Measurement_Point_Round-TH_Small
TP2: RailcomOLBCVRef; Measurement_Point_Round-TH_Small
TP3: RailcomVRef; Measurement_Point_Round-TH_Small
TP4: PROGPower; Measurement_Point_Round-TH_Small
TP5: OpsEnableTP; Measurement_Point_Round-TH_Small
TP6: BrakeTP; Measurement_Point_Round-TH_Small
TP7: OpsDigTP; Measurement_Point_Round-TH_Small
TP8: Prog_Signal; Measurement_Point_Round-TH_Small
TP9: Prog_Enable; Measurement_Point_Round-TH_Small
U1: LM2574N-5.0; DIP-8_W7.62mm
U2: TCAN332DR; SOIC-8-1EP_3.9x4.9mm_Pitch1.27mm
U3: LMD18200; TO220_11PIN_VERT
U4: L298N; TO127P2020X500X2100-15
U5, U8: LM358; DIP-8_W7.62mm
U6: LM339; DIP-14_W7.62mm
U7: TMP36; TO-92_Molded_Narrow

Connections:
+3V3: C6.1, C8.1, D5.2, D6.2, P1.14, P2.23, R4.1, R12.1, R14.1, R15.1, R21.1, R22.2, R28.1, R29.1, R37.1, U2.3, U5.8, U6.3, U6.8, U7.1, U8.8
+5V: C3.1, C13.1, J101.1, L1.2, P1.1, P1.5, TP1.1, U1.1, U4.9
/CAN1_RX: P2.25, U2.4, U8.3
/CAN1_TX: P2.27, U2.1, U8.5
/DCC_VS: C4.1, C9.2, D1.1, Q1.3, R6.2, R25.1, R26.1, R31.1, U1.5, U3.6
/FAN-CONTROL: P1.34, R30.2
/OLBC_A: J3.5, J4.5, Q14.2, U4.13
/OLBC_B: J3.4, J4.4, Q17.2, U4.14
/OPS-BRAKE: P2.8, R12.2, TP6.1, U3.4
/OPS-ENABLE: P2.35, R10.1, TP5.1, U3.5, U4.11
/OPS-SENSE: C10.2, P1.19, R13.2, U3.8
/OPS-SIG: P2.24, R11.1, R502.1, TP7.1, U3.3, U4.10
/OPS-THERM: P2.33, U3.9
/OPS_A: C1.2, C11.2, D8.2, F102.2, Q5.2, U3.2
/OPS_B: C12.2, D9.2, F101.2, Q12.2, R1.1, U3.10
/PROG-ENABLE: P1.2, TP9.1, U4.6
/PROG-SENSE: P1.21, R18.1, U5.1
/PROG-SIG: P1.4, R501.1, TP8.1, U4.5
/PROG_DCC_VS: Q2.1, TP4.1, U4.4
/Prog and LCC Alt H/L Driver/1A: F103.2, R2.2, U4.2
/Prog and LCC Alt H/L Driver/1B: C2.2, F104.2, U4.3
/RAILCOM-DATA: D7.2, P2.5, R28.2, U6.2, U6.13
/RAILCOM-DIR: D7.1, P2.3, R29.2, U6.1
/RAILCOM-ENABLE: P2.18, Q11.2, R27.1
/RAILCOM-SHORT: P2.22, Q7.3, Q8.2, Q9.3, Q15.3, Q16.3, R22.1
/RAILCOM_OLBC_VREF: C17.1, R37.2, R38.1, TP2.1, U6.11
/RAILCOM_VREF: C5.1, R4.2, R5.1, TP3.1, U6.5, U6.7
/Railcomm Interface/GATE-EN: Q5.1, Q6.3, Q10.3, Q12.1, Q14.1, Q17.1, R25.2
/TEMP-SENSE: P1.23, U7.2
GND: C3.2, C4.2, C5.2, C6.2, C7.2, C8.2, C9.1, C10.1, C13.2, C14.2, C15.2, C16.2, C17.2, D2.2, J3.3, J3.6, J3.7, J4.3, J4.6, J4.7, J6.1, J101.4, J101.5, P1.13, P1.15, P1.16, P1.22, P2.15, P2.21, Q3.1, Q4.1, Q6.1, Q7.1, Q8.1, Q9.1, Q10.1, Q11.1, Q13.3, Q15.1, Q16.1, R3.2, R5.2, R10.2, R11.2, R13.1, R16.2, R17.2, R20.1, R24.2, R27.2, R33.1, R35.2, R38.2, R41.2, R42.2, T1.1, T1.3, T2.2, T3.2, U1.2, U1.3, U1.4, U2.2, U3.7, U4.8, U4.15, U5.4, U6.9, U6.12, U7.3, U8.4
unnamed: C1.1, R1.2
unnamed: C2.1, R2.1
unnamed: C7.1, J2.3, J2.4
unnamed: C11.1, U3.1
unnamed: C12.1, U3.11
unnamed: C14.1, R19.1, U6.4
unnamed: C15.1, R23.1, U6.6
unnamed: C16.1, R34.1, U6.10
unnamed: D1.2, T1.2
unnamed: D2.1, L1.1, U1.7
unnamed: D3.1, T2.1
unnamed: D3.2, D4.1, J3.8, J4.8
unnamed: D4.2, T3.1
unnamed: D5.1, R39.1
unnamed: D6.1, R40.1
unnamed: D8.1, R41.1
unnamed: D9.1, R42.1
unnamed: F101.1, J1.1
unnamed: F102.1, J1.2
unnamed: F103.1, J1.3
unnamed: F104.1, J1.4
unnamed: J2.1, R8.2
unnamed: J2.2, R9.2
unnamed: J3.1, J4.1, R9.1, U2.7
unnamed: J3.2, J4.2, R8.1, U2.6
unnamed: J5.1, R31.2
unnamed: J5.2, Q13.2
unnamed: J6.4, P1.32
unnamed: J6.5, P1.30
unnamed: J101.2, P1.9
unnamed: J101.3, P1.11
unnamed: Q1.1, Q2.2, R3.1
unnamed: Q1.2, R7.2
unnamed: Q2.3, R6.1, R7.1
unnamed: Q3.2, R501.2
unnamed: Q3.3, R14.2, U4.7
unnamed: Q4.2, R502.2
unnamed: Q4.3, R15.2, U4.12
unnamed: Q5.3, Q7.2, R19.2, R20.2
unnamed: Q6.2, Q8.3, R21.2
unnamed: Q10.2, Q11.3, R26.2
unnamed: Q9.2, Q12.3, R23.2, R24.1
unnamed: Q13.1, R30.1
unnamed: Q14.3, R32.2
unnamed: Q15.2, R32.1, R33.2
unnamed: Q16.2, R34.2, R35.1, R36.2
unnamed: Q17.3, R36.1
unnamed: R16.1, U4.1, U5.3
unnamed: R17.1, R18.2, U5.2
unnamed: R39.2, U8.6, U8.7
unnamed: R40.2, U8.1, U8.2

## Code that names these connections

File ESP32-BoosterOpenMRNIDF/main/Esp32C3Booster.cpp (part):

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
    GpioInit::hw_init();
    TempSense_Pin::hw_init();
    CurrentSense_Pin::hw_init();

    Esp32C3Booster::NvsManager nvs;
    nvs.init(reset_reason);
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    
    FanControl fan(stack.node(), cfg.seg().fancontrol(), 
                   TempSense::instance(),
                   FAN_Control_Pin::instance());
    HBridgeControl mains(stack.node(),cfg.seg().maindcc(), 
                         CurrentSense::instance(),
                         MAIN_MAX_MILLIAMPS, MAIN_LIMIT_MILLIAMPS, 
                         Brake_Pin::instance());
    
    openlcb::RefreshLoop refresh_loop(stack.node(), {
                                      fan.polling()
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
